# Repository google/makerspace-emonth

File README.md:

# Makerspace EMonth Class

This is a class that started at the Mountain View makerspace called the Garage, where we have a series of classes that teaches you hands-on electronics.

The current edition (2017) features two sessions, numbered (session).(week) in subdirectories with resources where they're first introduced.

First Session (June)

* class1.1 - Soldering skills, Raspberry Pi
* class1.2 - Resistor Dividers, LCDs
* class1.3 - Coding, ADC, Interrupts, Arduino (Uno)
* class1.4 - Making it look professional

Second Session (July)

* class2.1 - Scary Mains, Rectification, Capacitors
* class2.2 - Current, Linear Regulation
* class2.3 - Transients and switch-mode converters, Shunts
* class2.4 - Constant Voltage and Constant Current
* class2.5 - Fancy MCU control

If you'd like to contribute, see [CONTRIBUTING](CONTRIBUTING.md)

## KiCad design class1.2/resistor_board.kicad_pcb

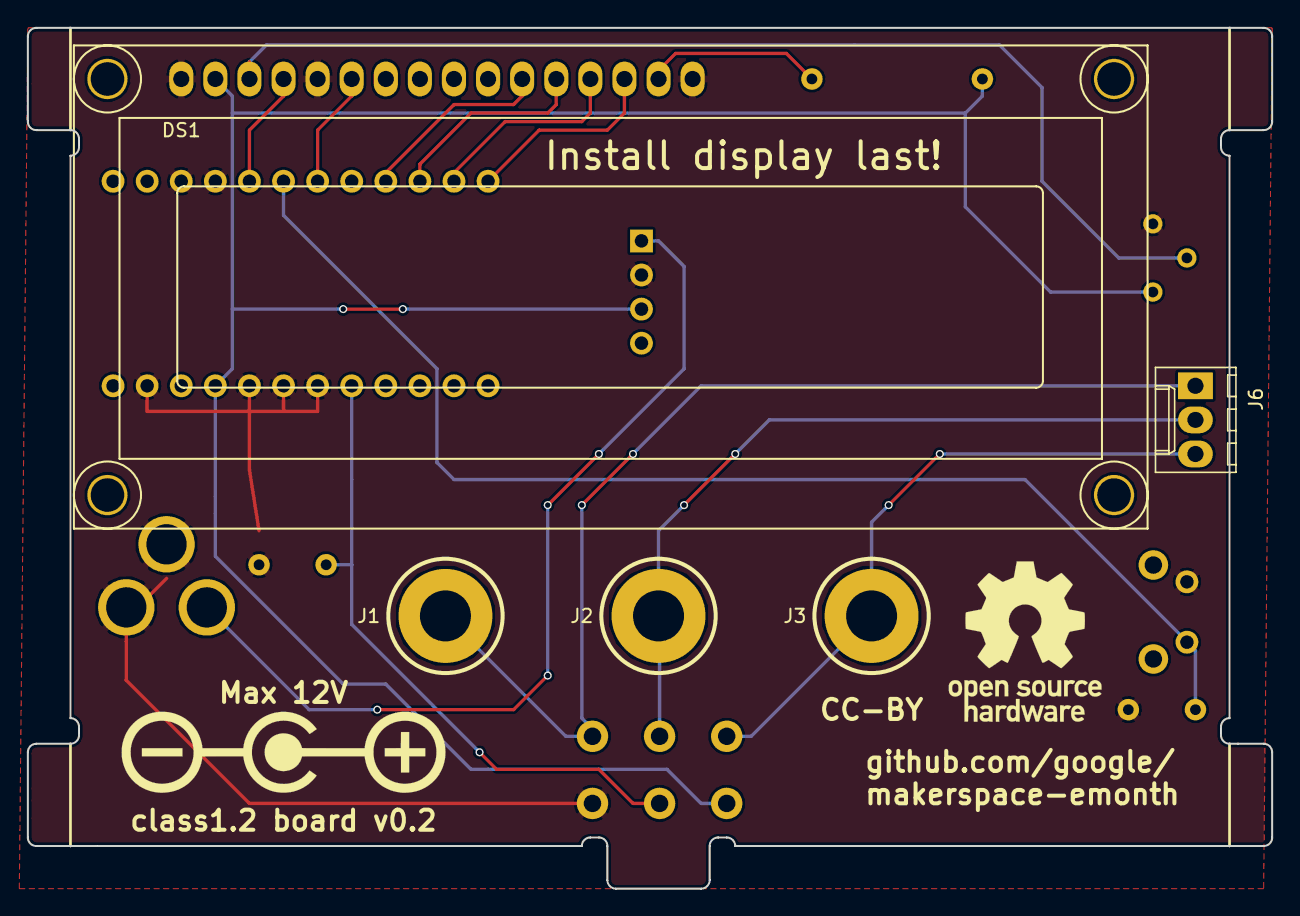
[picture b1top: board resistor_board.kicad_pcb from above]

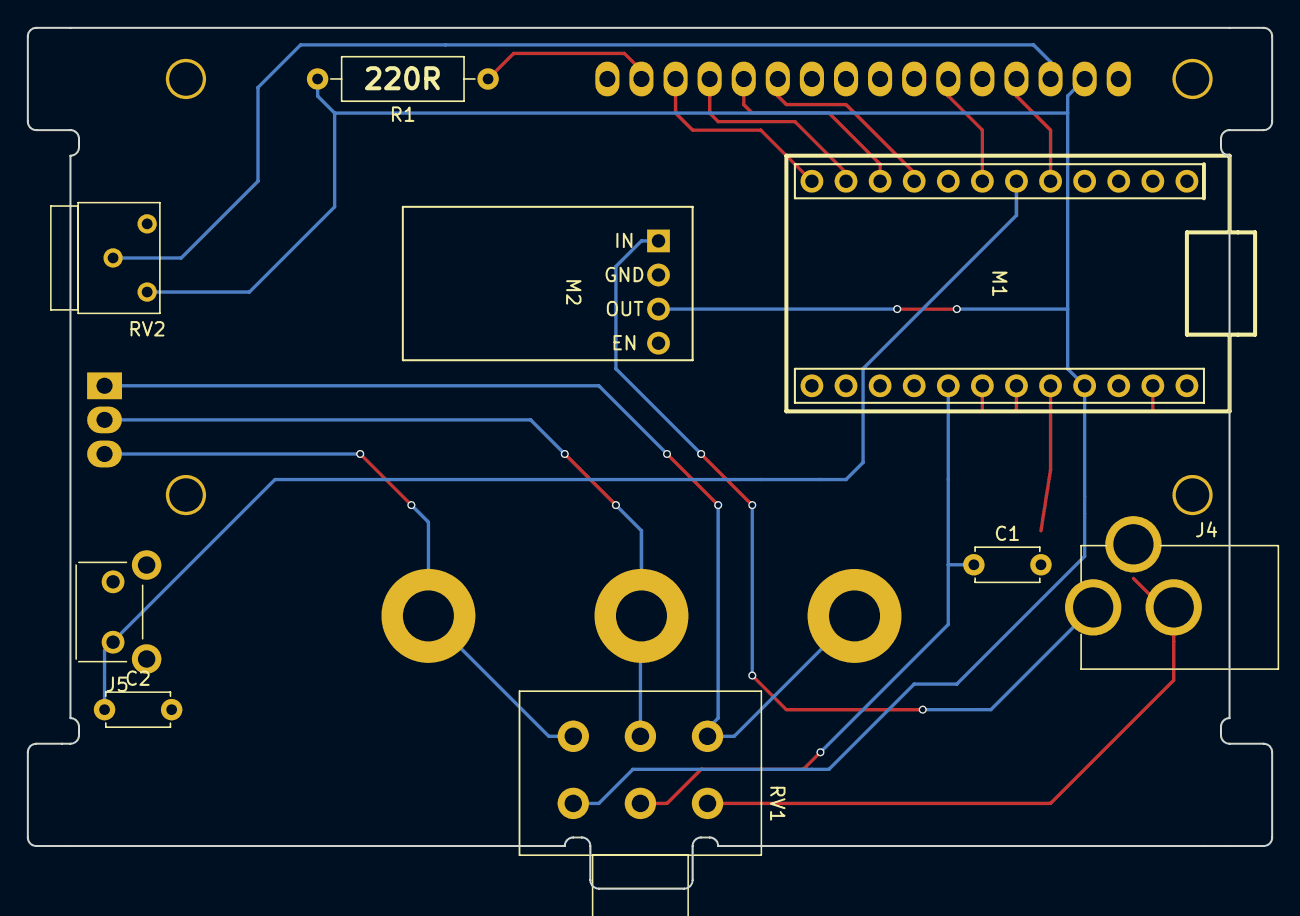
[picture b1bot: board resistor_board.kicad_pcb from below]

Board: 2 copper layers, 92.7 x 64.1 mm, 16 parts (9 on the bottom side), 16 nets.

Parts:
C1, C2: 0.1; C_Disc_D4.7mm_W2.5mm_P5.00mm
DS1: LCD16X2; WC1602A
J1, J2, J3: CONN_01X01; BANANA_VIA
J4: BARREL_JACK
J5: CONN_01X02; SW_Tactile_SKHH_Angled
J6: CONN_01X03; Molex_KK-6410-03_03x2.54mm_Straight
M1: ADUINO_MICRO; Arduino_Micro
M2: BuckModule
P1: SYMBOL; Polarity_Center_Positive_6mm_SilkScreen
P2: SYMBOL; OSHW-Logo_11.4x12mm_SilkScreen
R1: 220R; R_Axial_DIN0309_L9.0mm_D3.2mm_P12.70mm_Horizontal
RV1: POT_Dual; Potentiometer_Alps_RK163_Double_Vertical
RV2: POT_TRIM; Potentiometer_Trimmer_Bourns_3339W_Vertical

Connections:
+5V: DS1.2, M1.21, M2.3, R1.2, RV1.1, RV2.1
BUTTON: C2.1, J5.2, M1.6
GND: C1.2, C2.2, DS1.1, DS1.5, DS1.16, J4.2, J4.3, J5.1, M1.3, M1.4, M1.18, M1.19, M1.20, M1.23, M2.2, RV1.3, RV2.3
LCD_CONTRAST: DS1.3, RV2.2
LCD_D4: DS1.11, M1.9
LCD_D5: DS1.12, M1.10
LCD_D6: DS1.13, M1.11
LCD_D7: DS1.14, M1.12
LCD_E: DS1.6, M1.7
LCD_RS: DS1.4, M1.5
unnamed: DS1.15, R1.1
unnamed: J1.1, J6.1, RV1.6
unnamed: J2.1, J6.2, RV1.5
unnamed: J3.1, J6.3, RV1.4
unnamed: J4.1, M2.1
POT_INPUT: C1.1, M1.17, RV1.2

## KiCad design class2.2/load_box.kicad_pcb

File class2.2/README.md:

At its core, this circuit is an electronic load connected to a small processor
for control.  For background on electronic loads, see
<http://powersupply.blogs.keysight.com/2012/08/how-does-electronic-load-regulate-its.html>
and also <https://wiki.analog.com/university/courses/electronics/text/chapter-4>
and for more opamp overview, <http://www.ti.com/lit/an/slaa068b/slaa068b.pdf>

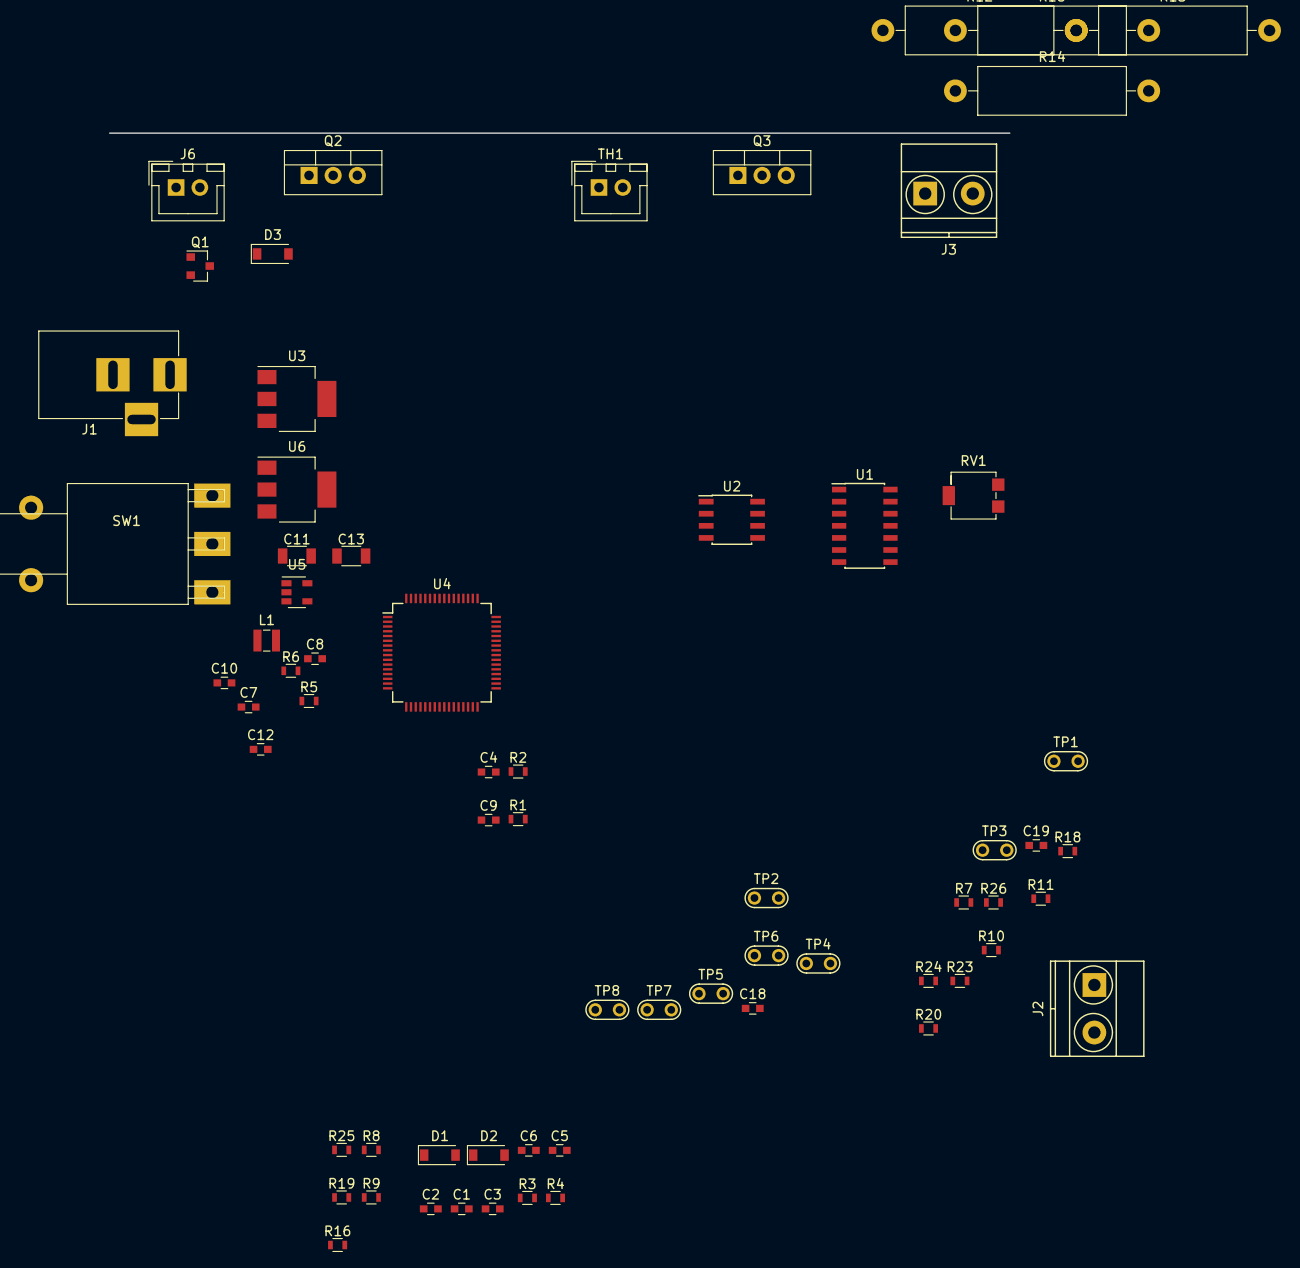
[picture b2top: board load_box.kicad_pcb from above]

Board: 2 copper layers, 66 parts (0 on the bottom side), 35 nets, no tracks yet.

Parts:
C1, C2, C3, C4, C5, C6, C9: C; C_0603
C7, C8: 1u; C_0603
C10, C12: 0.1u; C_0603
C11, C13: 10u; C_1206
C18, C19: 0.1; C_0603
D1, D2, D3: D; D_SOD-123
J1: BARREL_JACK
J2, J3: Screw_Terminal_1x02; TerminalBlock_Pheonix_MKDS1.5-2pol
J6: CONN_01X02; JST_XH_B02B-XH-A_02x2.50mm_Straight
L1: 10uH; L_Wuerth_MAPI-2510
Q1: Q_NMOS_GDS; SOT-23
Q2, Q3: Q_NMOS_GDS; TO-220_Vertical
R1, R2, R3, R4, R7, R8, R9, R10, R18, R19, R20, R23, R24, R25, R26: R; R_0603
R5: 90.9k; R_0603
R6: 8.45k; R_0603
R11, R16: 100R; R_0603
R12, R13, R14, R15: R; R_Axial_DIN0516_L15.5mm_D5.0mm_P20.32mm_Horizontal
RV1: POT_TRIM; Potentiometer_Trimmer_Bourns_3214G
SW1: SW_SPST; SW_SPDT
TH1: Thermistor_NTC; JST_XH_B02B-XH-A_02x2.50mm_Straight
TP1, TP2, TP3, TP4, TP5, TP6, TP7, TP8: TEST; Test_Point
U1: LM324; SOIC-14_3.9x8.7mm_Pitch1.27mm
U2: INA128; SOIC-8_3.9x4.9mm_Pitch1.27mm
U3: LD1117S50TR; SOT-223
U4: STM32L152RCTx; LQFP-64_10x10mm_Pitch0.5mm
U5: AP3012; SOT-23-5
U6: LD1117S33TR; SOT-223

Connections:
+3V3: C2.2, C3.2, C5.1, C11.1, U6.2
+5V: C13.1, R1.1, U3.2
+12V: C18.1, C19.1, D3.1, J6.1, R18.1, RV1.1, TP4.1, U1.4, U2.7
+BATT: C7.1, C10.1, C12.1, L1.1, SW1.2, U3.3, U5.5, U6.3
/load_box_display/+13V: C8.1, R5.1
/load_box_mcu/CHOSEN_VREF: R20.1, TP1.1, U4.40
/load_box_mcu/MEASURED_VREF: U1.6, U1.7, U4.10
GND: C1.1, C2.1, C3.1, C4.2, C5.2, C6.2, C7.2, C8.2, C10.2, C11.2, C12.2, C13.2, C18.2, C19.2, D2.1, J1.2, J1.3, J3.2, Q1.3, R2.2, R3.1, R6.2, R7.2, R12.2, R13.2, R14.2, R15.2, R26.2, RV1.3, TH1.2, U1.11, U2.4, U2.5, U3.1, U4.12, U4.18, U4.31, U4.47, U4.63, U5.2, U6.1
unnamed: C9.2, R2.1
unnamed: D1.1, D2.2
unnamed: D1.2, R4.2
unnamed: D3.2, J6.2, Q1.2
unnamed: L1.2, U5.1
unnamed: J1.1, SW1.1
unnamed: J2.1, R23.1
unnamed: J2.2, R25.2, R26.1
unnamed: J3.1, Q2.2, Q3.2
unnamed: Q1.1, R10.1
unnamed: Q2.1, R11.1, TP5.1
unnamed: Q2.3, Q3.3, R9.1, R12.1, R13.1, R14.1, R15.1
unnamed: Q3.1, R16.1, TP8.1
unnamed: R5.2, R6.1, U5.3
unnamed: R8.1, R9.2, TP3.1, U1.1, U1.13
unnamed: R8.2, U1.2
unnamed: R10.2, U1.8
unnamed: R11.2, R16.2, U1.14
unnamed: R18.2, TH1.1, U1.9
unnamed: R19.1, U2.1
unnamed: R19.2, U2.8
unnamed: R7.1, R20.2, TP2.1, U1.3
unnamed: R23.2, R24.1, TP6.1, U2.3
unnamed: R24.2, R25.1, TP7.1, U2.2
unnamed: RV1.2, U1.10
unnamed: U1.5, U2.6
USERB: C9.1, R1.2

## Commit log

2017-04-12 Initial commit on emonth
2017-04-13 Add gitignore
2017-04-13 Add roughed-in version of the load box.
2017-04-14 Moving class2.2 forward, includes 13V switching converter.
2017-04-14 Add connector library for FPC-30
2017-04-15 checkpoint some analog
2017-04-17 Snapshot with basic MCU, analog
2017-04-18 Further layout.
2017-04-18 Add napkin sketch
2017-04-19 Checkpoint with NHD, 3.3v, and layout
2017-04-19 Add Class 1.2 resistor board, ready for first tests
    (Will follow up with working fp-lib-table)
2017-06-23 Resistor board v0.2
2017-06-23 Shuffle more footprints.
2017-06-23 Include fp-lib-table

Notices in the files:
class1.2/resistor_board.kicad_pcb:
CC-BY
